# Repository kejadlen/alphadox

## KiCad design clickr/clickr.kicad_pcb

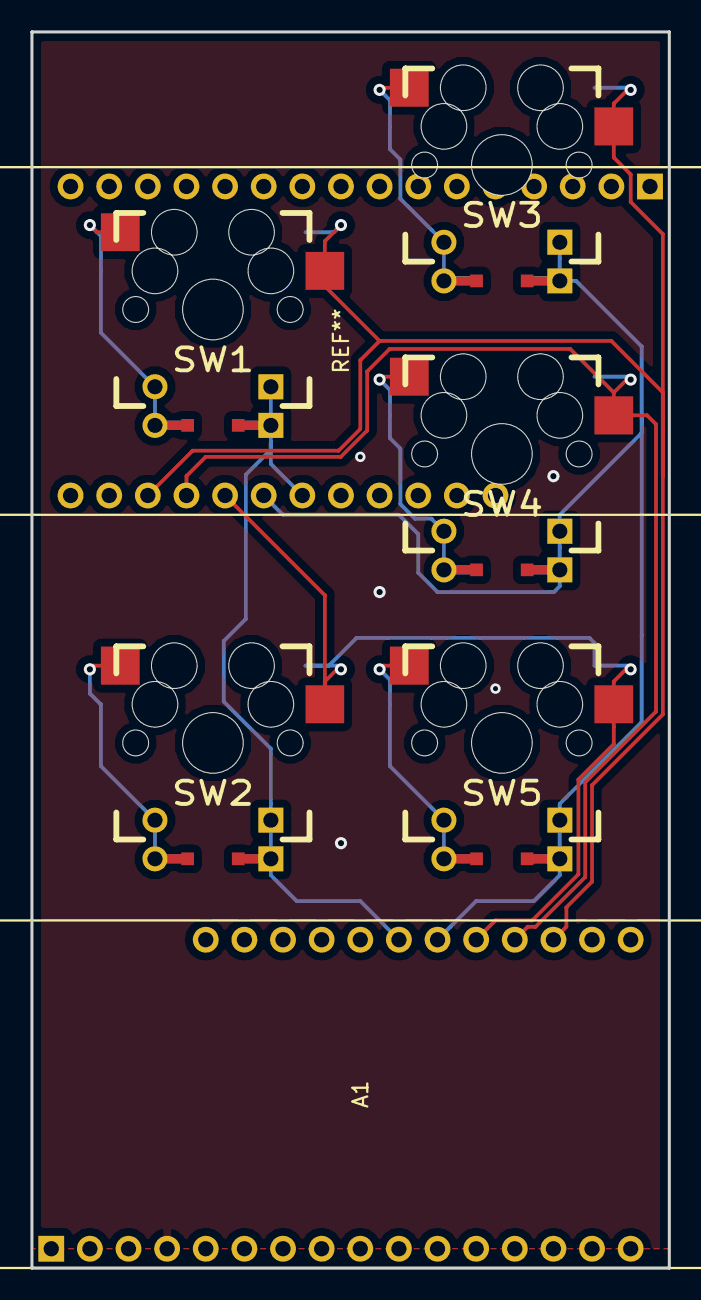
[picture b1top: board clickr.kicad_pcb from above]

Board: 2 copper layers, 41.9 x 81.3 mm, 6 parts (0 on the bottom side), 10 nets.

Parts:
A1: Feather_M0_Bluefruit
SW1: 0:0; MX_SOCKET_FLIP_DIODE
SW2: 2:0; MX_SOCKET_FLIP_DIODE
SW3: 0:1; MX_SOCKET_FLIP_DIODE
SW4: 1:1; MX_SOCKET_FLIP_DIODE
SW5: 2:1; MX_SOCKET_FLIP_DIODE

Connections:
/COL0: A1.22, SW1.4, SW2.4
/COL1: A1.23, SW3.4, SW4.4, SW5.4
/ROW0: A1.26, SW1.1, SW3.1
/ROW1: A1.25, SW4.1
/ROW2: A1.24, SW2.1, SW5.1
unnamed: SW1.2, SW1.3
unnamed: SW2.2, SW2.3
unnamed: SW3.2, SW3.3
unnamed: SW4.2, SW4.3
unnamed: SW5.2, SW5.3

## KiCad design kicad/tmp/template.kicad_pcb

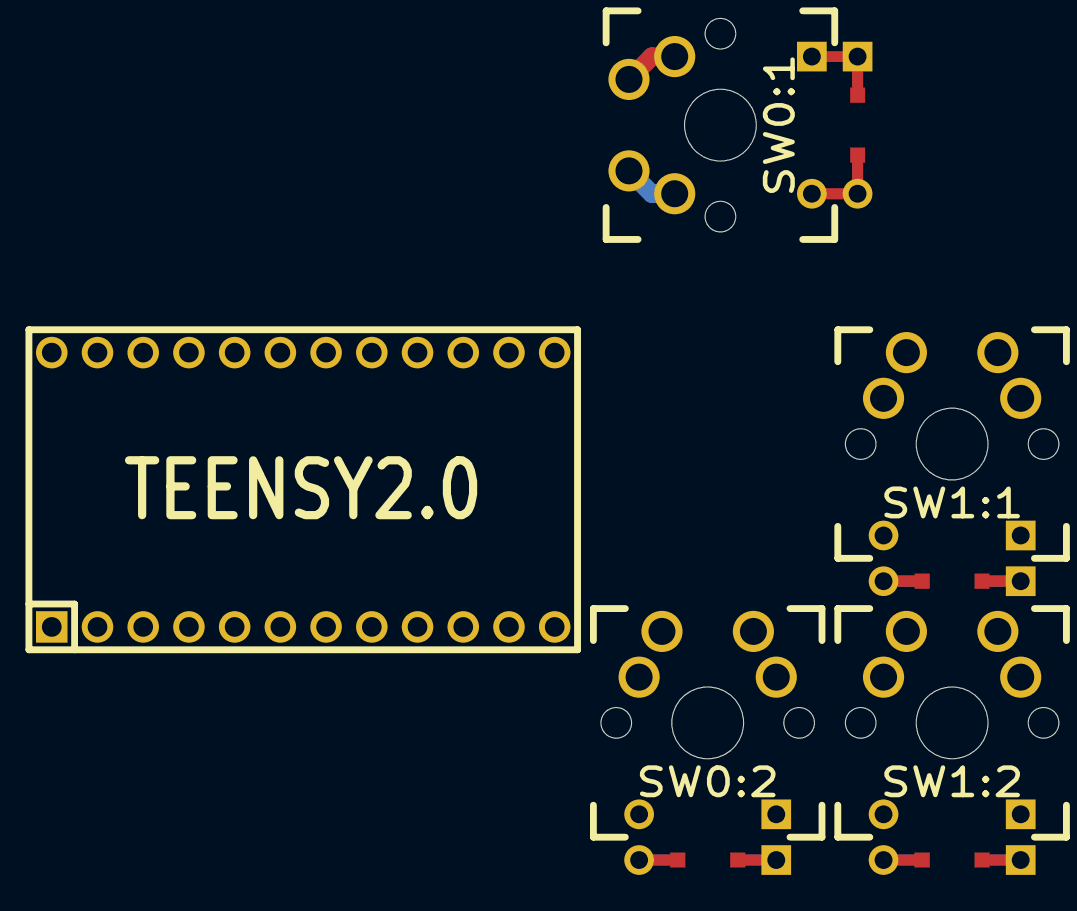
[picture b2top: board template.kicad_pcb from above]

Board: 2 copper layers, 5 parts (0 on the bottom side), 8 nets.

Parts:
SW0:1: SW0:1; MX_FLIP_DIODE
SW0:2: SW0:0; MX_FLIP_DIODE
SW1:1: SW1:1; MX_FLIP_DIODE
SW1:2: SW1;0; MX_FLIP_DIODE
U1: TEENSY2.0; TEENSY_2.0

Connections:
/COL0: SW0:2.4, SW1:2.4, U1.5
/COL1: SW0:1.4, SW1:1.4, U1.4
/ROW0: SW0:1.1, SW0:2.1, U1.3
/ROW1: SW1:1.1, SW1:2.1, U1.2
unnamed: SW0:1.2, SW0:1.3
unnamed: SW0:2.2, SW0:2.3
unnamed: SW1:1.2, SW1:1.3
unnamed: SW1:2.2, SW1:2.3

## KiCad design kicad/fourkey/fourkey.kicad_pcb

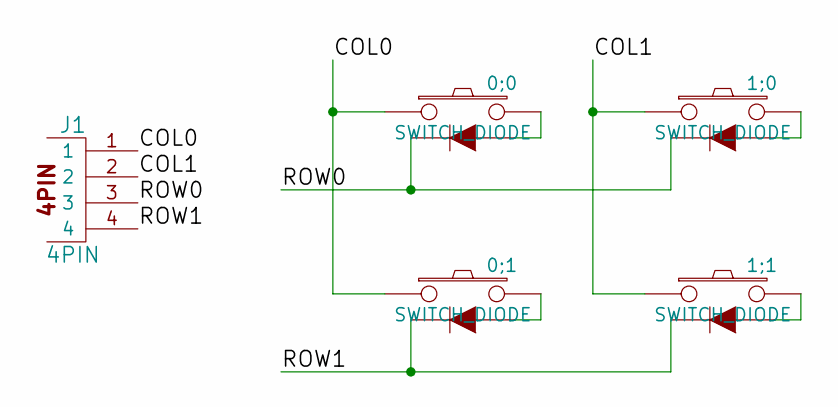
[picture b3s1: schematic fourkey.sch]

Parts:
0;0, 0;1, 1;0, 1;1: SWITCH_DIODE; MX_FLIP_DIODE
J1: 4PIN; Pin_Header_Straight_1x04

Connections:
/COL0: 0;0.1, 0;1.1, J1.1
/COL1: 1;0.1, 1;1.1, J1.2
/ROW0: 0;0.4 (K), 1;0.4 (K), J1.3
/ROW1: 0;1.4 (K), 1;1.4 (K), J1.4
GND: 0;0.0 (GND), 0;1.0 (GND), 1;0.0 (GND), 1;1.0 (GND)
unnamed: 0;0.2, 0;0.3 (A)
unnamed: 0;1.2, 0;1.3 (A)
unnamed: 1;0.2, 1;0.3 (A)
unnamed: 1;1.2, 1;1.3 (A)

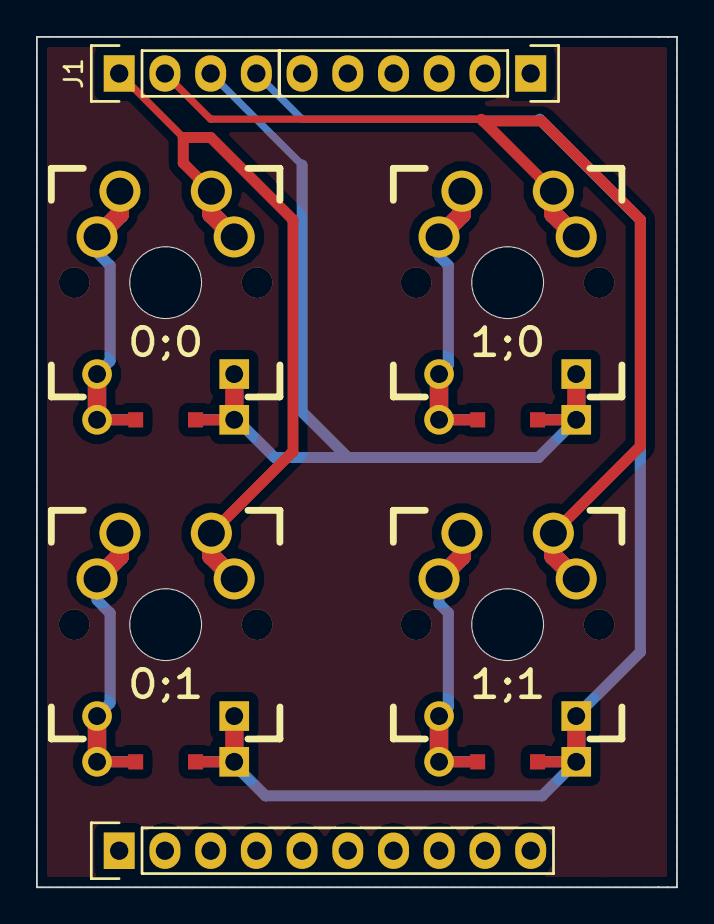
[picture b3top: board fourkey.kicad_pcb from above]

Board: 2 copper layers, 35.6 x 47.2 mm, 7 parts (0 on the bottom side), 9 nets.

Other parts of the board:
Pin_Header_Straight_1x06: VAL**; Pin_Header_Straight_1x06
Pin_Header_Straight_1x10: VAL**; Pin_Header_Straight_1x10

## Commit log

2014-11-12 Add kerf_test
2014-11-12 Add switch hole for testing -0.05mm kerf
2014-11-12 Fix references in README
2014-11-12 Credit where credit's due
2014-11-27 Make a single-key keyboard
2014-11-27 Make SVG page smaller
2014-11-27 Use squares instead of overloading switch hole
2014-11-27 Change washer size
2014-11-27 Initial case
2014-11-27 Finalized non-rotated case
2014-11-28 Make one_key more like alphadox
2014-11-28 Give the alphadox reference square a red stroke
2014-11-29 Add rotation to the case
2014-11-29 Update DXF/SVG files for the case
2014-11-29 Add staggering and better rotation maths
2014-11-29 Adjust column staggering
2014-11-29 Add specs for cutting a test plate
    For testing hand separation, kerf, and screw offset.
2014-12-01 Update test plate output
2014-12-02 Increase resolution of SCAD files for screws
2014-12-02 Add 40% keyboard
2014-12-04 Rename 40% to αXL
2014-12-24 Update αXL
2015-01-04 First draft of a Planck-esque plate
2015-01-04 More work on the Planck
2015-01-04 Save point for Alpheus
2015-01-07 Moar Planck
2015-01-07 Fix attribution
2015-01-07 Change screw holes from 3mm to 2.5mm
2015-03-02 Remove unused OpenSCAD files
2015-03-02 s/alpheus/planckeus/
2015-03-03 Add tmk_keyboard submodule
2015-03-03 Bump tmk_keyboard submodule
2015-03-03 s/case/openscad/
2015-03-03 Add KiCAD files for the ergodox
2015-03-03 [planckeus] Move USB micro breakout to the side of the case
2015-03-06 KiCAD
2015-03-08 Mostly fourkey PCB work
2015-03-09 More FourKey work, including Gerber files
2015-03-09 Use relative path for KiCAD project
2015-03-14 Bump tmk_keyboard
2015-03-15 Create modern KiCAD footprint library
2015-03-17 Small refactor of planckeus.scad
2015-03-17 AlphaDox test plate
    Create a test plate for the AlphaDox that follows the Ergodox layout
    pretty closely.
2015-03-18 More radical AlphaDox layout
2015-03-18 Compressed AlphaDox test plate
2015-03-21 KeyBoardLayout spike
    Probably should've commited this earlier. Oh well!
2015-03-21 Implement rotation
2015-03-21 Test nesting transforms
2015-03-21 Move Key into KBL
2015-03-21 Turn KBL into a library
2015-03-21 Some refactoring of KBL
2015-03-21 SCAD transformer for KBLs
2015-03-21 s/KBL/Alphadox::Layout
2015-03-21 Add initial Layout->SCAD code
2015-03-22 Remove xy param to `key`
2015-03-22 Use associative property of matrix multiplication
2015-03-22 Simplify affine transforms
2015-03-23 Fix key rotation
2015-03-23 Add screws to layout
2015-03-23 Implement edge cuts
2015-03-23 Fix fourkey drill file
2015-03-23 Add Alphadox layout
2015-03-23 Add alphadox.scad from layout
2015-03-23 Update Alphadox layout
2015-03-24 s/scripts/src
2015-04-07 Add holes to layout
2015-04-08 Quick and dirty s-expression parser
2015-05-03 Refactoring of SCAD generator
2015-05-14 Rotate clockwise instead of counter-clockwise
2015-05-14 Fix edge cuts in SCAD generation
2015-09-03 Added Gitter badge
2016-12-04 I have no idea what's in here
    Came back to this project to find all these changes. I have no idea what
    they are, so here's a random commit! I hope these changes are good!
2018-08-20 update ergodox kicad project kicad 5
2018-09-12 add datasheets for hot swap sockets and mx switches
2018-09-12 remove tmk_keyboard submodule
2018-09-12 clickr
2018-09-15 tweak positioning of switch plate
2019-11-23 housecleaning
2022-12-31 Add renovate.json
2023-01-21 bump ruby
2023-01-21 add keyboardio kicad libraries submodule
2023-01-21 add qmk kicad libraries submodule
2023-01-23 add keebio submodule
